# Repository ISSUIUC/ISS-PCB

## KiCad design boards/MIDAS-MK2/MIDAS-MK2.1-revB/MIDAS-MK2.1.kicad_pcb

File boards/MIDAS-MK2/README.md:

# MIDAS MK2

MIDAS MK2 is the new and improved generation of the Illinois Space Society's MIDAS flight computer. Continuing MIDAS’s mission as the centerpiece of a flexible avionics ecosystem, MK2 features data acquisition, live telemetry, board-to-board communication interfaces, and pyrotechnic capabilities for in-flight control. This new revision retains the diverse suite of sensors from the original and features upgraded pyro circuitry with an emphasis on redundancy and reliability. As the team pushes closer and closer to space, MK2 employs a new generation of LoRa radios with 60% higher transmit power as well as CAN and I2C connections for future expandability into satellite communications and other more advanced tracking capabilities. This adaptable nature has enabled MIDAS to fulfill various roles, not only as a flight computer but also as a part of the team’s onboard video system and as a major ground support device. Overall, these across-the-board improvements have pushed the MIDAS project to new heights and led to a string of successes in each of its many domains.

Three MIDAS MK2 boards have been produced, with the series successfully flying in flight control of the Stargazer 1.4 vehicle and as the primary tracker for Aether I & II, the latter of which flew to an altitude of 75,000 feet.

Read more about MIDAS and the surrounding avionics systems in the [MIDAS MK2 Report](https://uofi.box.com/s/k0ad6ryhxbzwpdwt33lxyxuxpivv3qhj).

# Schematics

Printable PDF schematics, diagrams, and layouts for MIDAS MK2.1 revA can be found in the PDFs and images folders.

# Graphics

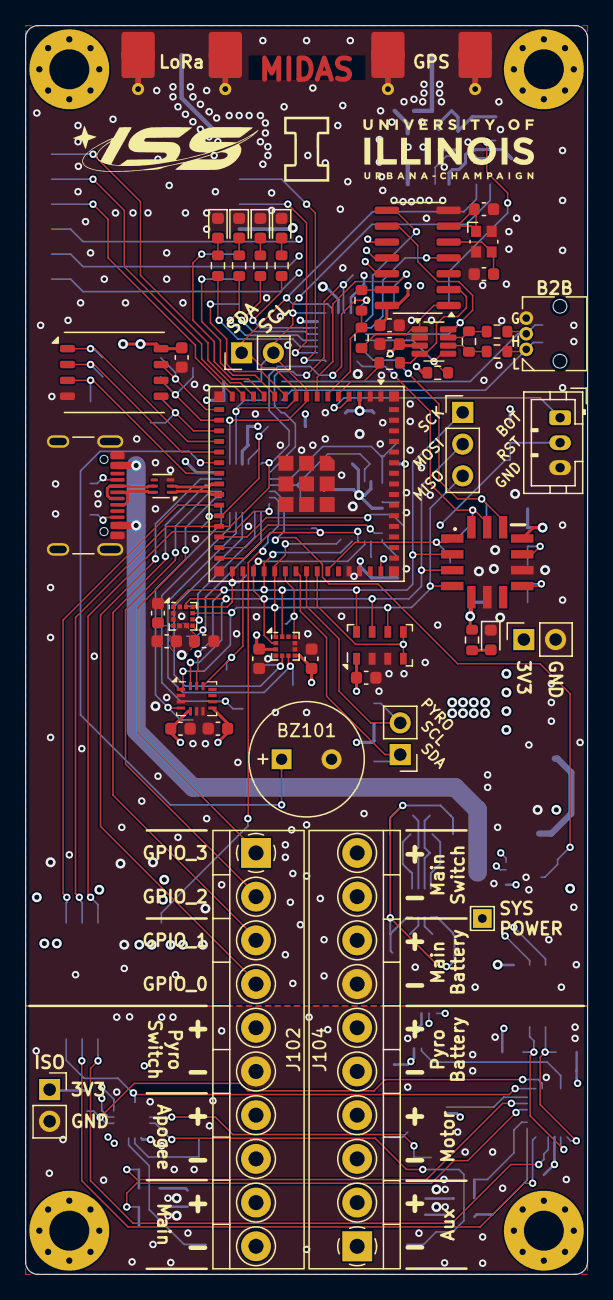
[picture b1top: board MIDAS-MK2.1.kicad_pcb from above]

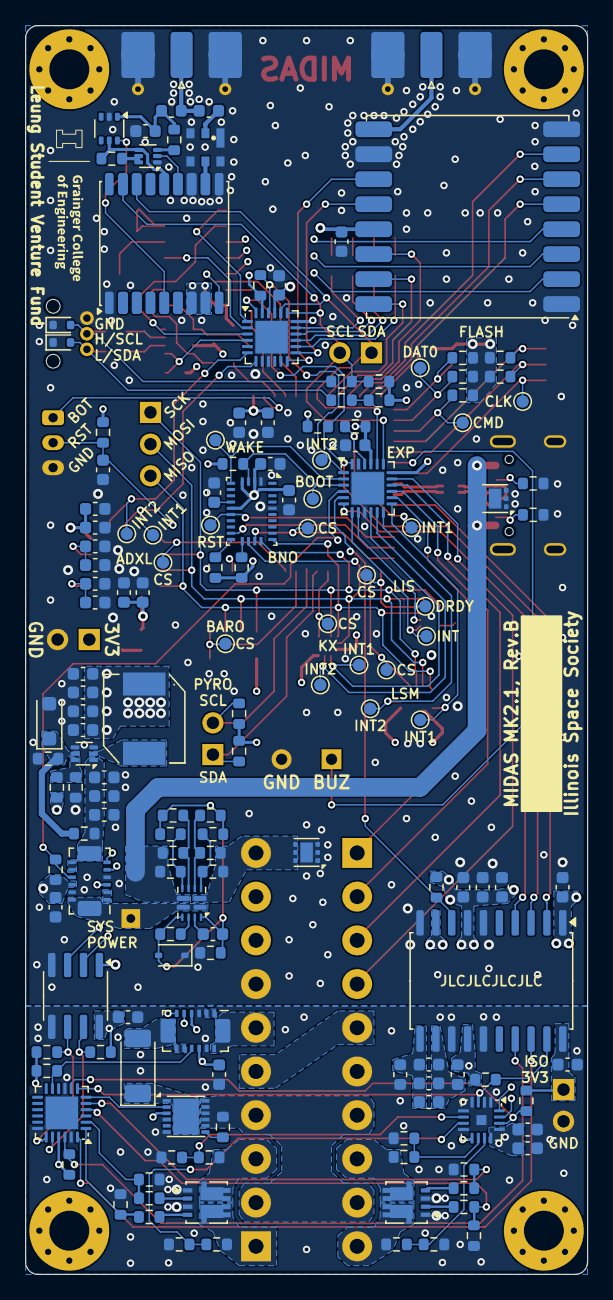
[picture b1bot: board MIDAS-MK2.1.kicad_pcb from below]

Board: 4 copper layers, 45.0 x 100.0 mm, 212 parts (155 on the bottom side), 155 nets.

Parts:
BZ101: AT-0927-TT-6-R; Buzzer_AT-0927-TT-6-R
C101, C102, C103, C107, C108, C109, C110, C201, C208, C209, C210, C211, C212, C301, C502, C504, C506, C507, C508, C510, C511, C512, C513, C514, C515, C517, C518, C519: 0.1uF; C_0603_1608Metric
C104, C105: 22pF; C_0603_1608Metric
C106, C304, C305, C306, C307: 22uF; C_0603_1608Metric
C111, C204, C205, C308, C501, C503, C505, C509, C516: 1uF; C_0603_1608Metric
C202, C203, C402: 10nF; C_0603_1608Metric
C206, C207, C302, C303, C401: 10uF; C_0603_1608Metric
C403: 47pF; C_0603_1608Metric
D101, D102: ESD321; D_SOD-523
D103, D303: RED LED; LED_0603_1608Metric
D104: ORANGE LED; LED_0603_1608Metric
D105: GREEN LED; LED_0603_1608Metric
D106: BLUE LED; LED_0603_1608Metric
D201: RSX501LAM20; D_SOD-128
D301: BZT52H-A5V1-QX; D_SOD-123F
D302: BAS416; D_SOD-323
FB201, FB202: BLM18SG331TN1D; L_0603_1608Metric
FL401: B3913; Qualcomm_SMD-6
H101, H102, H103, H104: M3; MountingHole_3.2mm_M3_Pad_Via
J101: USB4105-GF-A; USB_C_Receptacle_GCT_USB4105-xx-A_16P_TopMnt_Horizontal
J102: Left; Molex_Terminal-Block_393570010_1x10_P3.5mm
J103: Conn_01x03; Molex_Micro-Lock_2200980371_1x03_P1.25mm_Horizontal
J104: Right; Molex_Terminal-Block_393570010_1x10_P3.5mm
J105, J106: Conn_01x02; PinHeader_1x02_P2.54mm_Vertical
J107: Conn_01x03; PinHeader_1x03_P2.54mm_Vertical
J108: Conn_01x03; JST_PH_B3B-PH-K_1x03_P2.00mm_Vertical
J201, J302: Conn_01x02; PinSocket_1x02_P2.54mm_Vertical
J301: TestPoint; TestPoint_THTPad_1.5x1.5mm_Drill0.7mm
J401, J402: SMA; SMA_Molex_73251-2120_EdgeMount_Horizontal
L301: 2.2uH; L_TDK_SPM6530
L401: 27nH; L_0603_1608Metric
Q201, Q202: Si7232DN; Vishay_PowerPAK_1212-8_Dual
Q401: Si1016X; SOT-563
R101, R104, R105, R106, R220, R222: 4.7k; R_0603_1608Metric
R102, R103, R107, R108, R114, R201, R221, R223, R224, R501: 10k; R_0603_1608Metric
R109, R110, R111, R112, R113: 50k; R_0603_1608Metric
R115, R116, R117, R118, R119, R120, R121, R312: 0; R_0603_1608Metric
R122: 120; R_0603_1608Metric
R123, R124: 5.1k; R_0603_1608Metric
R125, R303: 20k; R_0603_1608Metric
R126, R127, R128, R129, R315: 470; R_0603_1608Metric
R202, R206, R207, R214, R215: 1k; R_0603_1608Metric
R203, R301, R302, R305, R308, R310: 5k; R_0603_1608Metric
R204, R205, R212, R213: 3.3k; R_0603_1608Metric
R208, R209, R216, R217, R402: 100k; R_0603_1608Metric
R210, R211, R218, R219, R306, R311: 30k; R_0603_1608Metric
R304: 27k; R_0603_1608Metric
R307: 33k; R_0603_1608Metric
R309: 69.8k; R_0603_1608Metric
R313: 135k; R_0603_1608Metric
R314: 21.5k; R_0603_1608Metric
R401: 10; R_0603_1608Metric
R502, R503: 2.2k; R_0603_1608Metric
TP101, TP102, TP103, TP104, TP105, TP106, TP107, TP108, TP109, TP110, TP111, TP112, TP113, TP114, TP115, TP116, TP117, TP118, TP119, TP120, TP121, TP122: TestPoint_Small; TestPoint_Pad_D1.0mm
U101, U201: INA745x; VQFN-REL0014B
U102, U103, U205: TCAL9539-Q1; WQFN-24-1EP_4x4mm_P0.5mm_EP2.6x2.6mm
U104: ESP32-S3-MINI-1U; ESP32-S2-MINI-1U
U105: MCP2518FDT-xSL; SOIC-14_3.9x8.7mm_P1.27mm
U106: ZDSD64GLGEAG-R; LGA-8_8x6.2mm_P1.27mm
U107: TCAN337G; SOT-23-8
U108: ECMF02-2AMX6; ST_UQFN-6L_1.5x1.7mm_P0.5mm
U202: NPC45560-H; DFN-12-1EP_3x3mm_P0.5mm_EP2.05x2.86mm
U203: ISOW7742; SOIC-20W_7.5x12.8mm_P1.27mm
U204: ISO1640BDR; SOIC-8_3.9x4.9mm_P1.27mm
U206: ADS122C04IRTE; Texas_RTE0016D_WQFN-16-1EP_3x3mm_P0.5mm_EP0.8x0.8mm
U301, U302: TVS1800DRV; WSON-6-1EP_2x2mm_P0.65mm_EP1x1.6mm
U303: TI_TPS566242; SOT-563
U304: TPS2121; Texas_VQFN-HR-12_2x2.5mm_P0.5mm
U401: RFM96W-433S2; HOPERF_RFM9XW_SMD
U402: NC7WZ07; SOT-363_SC-70-6
U403: MAX-M10S; ublox_MAX
U501: KX134-1211; LGA-12_2x2mm_P0.5mm
U502: ADXL355; Analog_LGA_14-7.4x7.4mm
U503: LSM6DSLTR; Bosch_LGA-14_3x2.5mm_P0.5mm
U504: BNO086; LGA-28_5.2x3.8mm_P0.5mm
U505: LIS3MDL; LGA-12_2x2mm_P0.5mm
U506: MS5611-01BA03; LGA-8_3x5mm_P1.25mm
Y101: 40MHz; Crystal_SMD_Abracon_ABM10-4Pin_2.5x2.0mm

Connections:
+3V3: C101.2, C102.1, C103.1, C106.2, C107.2, C108.2, C109.2, C110.2, C202.1, C204.1, C206.1, C209.1, C304.1, C305.1, C306.1, C307.1, C401.1, C501.2, C502.2, C503.2, C504.1, C506.1, C508.1, C511.1, C512.1, C514.1, C515.1, C516.2, C517.2, C519.1, J302.1, L301.1, R101.2, R102.2, R103.2, R104.2, R105.2, R106.2, R107.1, R108.2, R109.2, R110.2, R111.2, R112.2, R113.2, R114.1, R125.2, R203.1, R313.2, R315.1, R501.2, R502.2, R503.2, U101.3 (A1), U101.11 (VS), U102.18 (A0), U102.21 (VCC), U103.18 (A0), U103.21 (VCC), U103.23 (A1), U104.3 (3V3), U105.14 (VDD), U106.8 (VDD), U107.3 (VCC), U203.1 (V_{IO}), U203.7 (EN_IO1), U203.9 (V_{DD}), U204.1 (VCC1), U401.13 (3.3V), U403.7 (VCC_IO), U403.8 (VCC), U501.3 (IO_VDD), U501.7 (VDD), U502.5 (V_{DDIO}), U502.11 (V_{SUPPLY}), U503.5 (VDDIO), U503.8 (VDD), U504.3 (VDD), U504.5 (PS1), U504.10 (CLKSEL0), U504.28 (VDDIO), U505.5 (Vdd), U505.6 (Vdd_IO), U506.1 (VDD)
+3V3_ISO: C201.2, C208.1, C210.1, C211.1, C212.1, FB201.1, J201.1, R201.1, R220.2, R221.2, R222.2, R223.2, R224.2, U201.4 (A0), U201.11 (VS), U202.3 (VCC), U203.14 (EN_IO2), U203.20 (V_{ISOIN}), U204.8 (VCC2), U205.21 (VCC), U206.9 (REFP), U206.12 (AVDD), U206.13 (DVDD)
/ADC_RESET: U104.25 (IO21), U203.2 (INA)
/ADXL355_CS: TP107.1, U104.40 (RXD0), U502.1 (~CS/SCL)
/ADXL355_INT1: TP109.1, U103.7 (P06), U502.13 (INT2)
/ADXL355_INT2: TP108.1, U103.6 (P05), U502.12 (INT1)
/AUX_GPIO_0: J102.4, U102.17
/AUX_GPIO_1: J102.3, U102.16
/AUX_GPIO_2: J102.2, U102.15
/AUX_GPIO_3: J102.1, U102.14
/BNO086_BOOT: R501.1, TP106.1, U102.3 (P02), U504.4 (BOOTN)
/BNO086_CS: TP103.1, U104.30 (IO48), U504.18 (H_CSN)
/BNO086_INT: U104.29 (IO34), U504.14 (H_INTN)
/BNO086_RESET: TP104.1, U104.28 (IO33), U504.11 (NRST)
/BNO086_WAKE: TP105.1, U102.2 (P01), U504.6 (PS0/WAKE)
/BOOT_SW: J108.1, U104.4 (IO0)
/BUZZER: BZ101.1 (-), U104.21 (IO17)
/CANH: R117.1, R122.1, U107.7 (CANH)
/CANL: R115.1, R122.2, U107.6 (CANL)
/CAN_1: R119.1, R120.1, U104.6 (IO2)
/CAN_2: R121.1, U104.5 (IO1)
/CAN_FAULT: R114.2, U103.4 (P03), U107.5 (FAULT)
/CAN_NCS: R119.2, U105.13 (NCS)
/CAN_NINT: U103.2 (P01), U105.4 (~INT)
/CAN_NINT1: U103.1 (P00), U105.8 (~INT1/GPIO1)
/CAN_RXD: R121.2, U105.2 (RXCAN), U107.4 (RXD)
/CAN_SLNT: U103.3 (P02), U105.9 (~INT0/GPIO0/XSTBY), U107.8 (S)
/CAN_TXD: R120.2, U105.1 (TXCAN), U107.1 (TXD)
/D+: J101.A6 (D+), J101.B6 (D+), U108.6 (D+_out)
/D-: J101.A7 (D-), J101.B7 (D-), U108.5 (D-_out)
/EXP_INT0: U102.6 (P05), U203.4 (OUTC)
/EXP_INT1: R102.1, TP101.1, U102.22 (~INT), U104.26 (IO26)
/EXP_INT2: R103.1, TP102.1, U102.1 (P00), U103.22 (~INT)
/EXP_RESET: R108.1, U102.24 (~RESET), U103.24 (~RESET), U104.27 (IO47), U203.3 (INB)
/FLASH_CLK: TP121.1, U104.22 (IO18), U106.3 (CLK)
/FLASH_CMD: R113.1, TP120.1, U104.18 (IO14), U106.5 (CMD)
/FLASH_DAT0: R109.1, TP122.1, U104.17 (IO13), U106.6 (DAT0)
/FLASH_DAT1: R110.1, U104.16 (IO12), U106.7 (DAT1)
/FLASH_DAT2: R111.1, U104.19 (IO15), U106.1 (DAT2)
/FLASH_DAT3: R112.1, U104.20 (IO16), U106.2 (DAT3)
/I2C_SCL: J105.2, R104.1, R118.1, U102.19 (SCL), U103.19 (SCL), U104.8 (IO4), U403.17 (SCL)
/I2C_SDA: J105.1, R101.1, R116.1, U102.20 (SDA), U103.20 (SDA), U104.9 (IO5), U403.16 (SDA)
/INA_ALERT: R107.2, U101.10 (ALERT), U102.4 (P03)
/ISO_FLT: R203.2, U102.5 (P04), U203.8 (EN/FLT)
/KX134_CS: TP110.1, U104.36 (IO40), U501.10 (nCS)
/KX134_INT1: TP112.1, U102.10, U501.5 (INT1)
/KX134_INT2: TP111.1, U102.11, U501.6 (INT2)
/LED_BLUE: R129.1, U103.14
/LED_GREEN: R128.1, U103.15
/LED_ORANGE: R127.1, U103.16
/LED_RED: R126.1, U103.17
/LIS3MDL_CS: TP113.1, U104.31 (IO35), U505.10 (CS)
/LIS3MDL_DRDY: TP114.1, U102.8 (P07), U505.8 (DRDY)
/LIS3MDL_INT: TP115.1, U102.7 (P06), U505.7 (INT)
/LSM6DSLTR_INT1: TP117.1, U102.13, U503.4 (INT1)
/LSM6DSLTR_INT2: TP118.1, U102.12, U503.9 (INT2)
/LSM6DSL_CS: TP116.1, U104.32 (IO36), U503.12 (CS)
/MAX_RESET: U104.7 (IO3), U403.9 (~RESET)
/MS5611_CS: TP119.1, U104.39 (TXD0), U506.4 (CSB), U506.5 (CSB)
/PYRO_A: J102.8, Q201.5 (D2), R208.2
/PYRO_B: J102.10, Q201.6 (D1), R216.2
/PYRO_C: J104.3, Q202.6 (D1), R209.2
/PYRO_D: J104.1, Q202.5 (D2), R217.2
/PYRO_SCL: J106.2, R106.1, U101.6 (SCL), U104.38 (IO42), U204.3 (SCL1)
/PYRO_SDA: J106.1, R105.1, U101.5 (SDA), U104.37 (IO41), U204.2 (SDA1)
/PYRO_SW: J102.5, J104.5
/Power/MUX_CP2: R307.2, R308.1, U304.3 (CP2)
/Pyro Circuitry/ADC_DRDY: R224.1, U205.8 (P07), U206.14 (DRDY)
/Pyro Circuitry/ADC_RST_ISO: R223.1, U203.19 (OUTA), U205.7 (P06), U206.3 (RESET)
/Pyro Circuitry/EXP_INT_ISO: R221.1, U203.17 (INC), U205.22 (~INT)
/Pyro Circuitry/EXP_RST_ISO: U203.18 (OUTB), U205.24 (~RESET)
/Pyro Circuitry/FIRE_A: R204.1, R206.1, U205.5 (P04)
/Pyro Circuitry/FIRE_B: R212.1, R214.1, U205.4 (P03)
/Pyro Circuitry/FIRE_C: R205.1, R207.1, U205.2 (P01)
/Pyro Circuitry/FIRE_D: R213.1, R215.1, U205.1 (P00)
/Pyro Circuitry/GND2: C203.2, C205.2, C207.2, FB202.2, U203.11 (GND2)
/Pyro Circuitry/INA_ALRT_ISO: R201.2, U201.10 (ALERT), U205.11
/Pyro Circuitry/ISO_SCL: R222.1, U201.6 (SCL), U204.6 (SCL2), U205.19 (SCL), U206.16 (SCL)
/Pyro Circuitry/ISO_SDA: R220.1, U201.5 (SDA), U204.7 (SDA2), U205.20 (SDA), U206.15 (SDA)
/Pyro Circuitry/PYRO_EN: U202.2 (EN), U205.6 (P05)
/Pyro Circuitry/SENSE_A: R208.1, R210.2, U206.10 (AIN1)
/Pyro Circuitry/SENSE_B: R216.1, R218.2, U206.11 (AIN0)
/Pyro Circuitry/SENSE_C: R209.1, R211.2, U206.6 (AIN3)
/Pyro Circuitry/SENSE_D: R217.1, R219.2, U206.7 (AIN2)
/Pyro Circuitry/V_ISOOUT: C203.1, C205.1, C207.1, FB201.2, U203.12 (V_{ISOOUT})
/Pyro Circuitry/V_PYRO_ZONE: D201.2 (A), U201.7 (IS-)
/RESET_SW: C111.1, J108.2, R125.1, U104.45 (EN)
/RF/MAX_INT: U402.6 (Y1), U403.5 (EXTINT)
/RFM96W_CS: U104.15 (IO11), U401.5 (NSS)
/RFM96W_DIO1: U104.11 (IO7), U401.15 (DIO1)
/RFM96W_DIO2: U104.10 (IO6), U401.16 (DIO2)
/RFM96W_DIO3: U103.12, U401.11 (DIO3)
/RFM96W_DIO4: U103.13, U401.12 (DIO4)
/RFM96W_DIO5: U104.13 (IO9), U401.7 (DIO5)
/RFM96W_INT: U104.12 (IO8), U401.14 (DIO0)
/RFM96W_RESET: U104.14 (IO10), U401.6 (RESET)
/SPI_MISO: J107.3, U104.35 (IO39), U105.12 (SDO), U401.2 (MISO), U501.1 (SDO/ADDR), U502.4 (MISO/ASEL), U503.1 (SDO/SA0), U504.20 (H_SDA/H_MISO/TX), U505.9 (SDO/SA1), U506.6 (SDO)
/SPI_MOSI: J107.2, U104.33 (IO37), U105.11 (SDI), U401.3 (MOSI), U501.2 (SDI/SDA), U502.3 (MOSI/SDA), U503.14 (SDA), U504.17 (H_SA0_MOSI), U505.11 (SDA/SDI/SDO), U506.7 (SDI/SDA)
/SPI_SCK: J107.1, U104.34 (IO38), U105.10 (SCK), U401.4 (SCK), U501.12 (SCLK/SCL), U502.2 (SCLK/V_{SSIO}), U503.13 (SCL), U504.19 (H_SCL/SCK/RX), U505.1 (SCL/SPC), U506.8 (SCLK)
/SYS_POWER: J301.1, U101.13 (VBUS), U101.14 (IS+), U304.1 (OUT), U304.8 (OUT)
/USB_D+: U104.24 (IO20), U108.1 (D+_in)
/USB_D-: U104.23 (IO19), U108.2 (D-_in)
/USB_POWER: J101.A4 (VBUS), J101.A9 (VBUS), J101.B4 (VBUS), J101.B9 (VBUS), R301.1, R304.1, U301.4 (IN), U301.5 (IN), U301.6 (IN), U304.7 (IN1)
/VBAT: J104.10, R307.1, R309.1, U302.4 (IN), U302.5 (IN), U302.6 (IN), U304.2 (IN2)
/VBAT_PYRO: J104.6, U201.13 (VBUS), U201.14 (IS+)
/VREG_IN: C301.1, C302.1, C303.1, R303.1, U101.7 (IS-), U303.1 (VIN)
/V_PYRO: J102.7, J102.9, J104.2, J104.4, R202.1, U202.8 (VOUT), U202.9 (VOUT), U202.10 (VOUT), U202.11 (VOUT), U202.12 (VOUT)
GND: BZ101.2 (+), C101.1, C102.2, C103.2, C104.1, C105.2, C106.1, C107.1, C108.1, C109.1, C110.1, C111.2, C202.2, C204.2, C206.2, C209.2, C301.2, C302.2, C303.2, C304.2, C305.2, C306.2, C307.2, C401.2, C402.2, C501.1, C502.1, C503.1, C504.2, C505.1, C506.2, C507.2, C508.2, C509.1, C510.2, C511.2, C512.2, C513.2, C514.2, C515.2, C516.1, C517.1, C518.1, C519.2, D101.1 (A1), D102.1 (A1), D103.1 (K), D104.1 (K), D105.1 (K), D106.1 (K), D301.2 (A), D302.1 (K), D303.1 (K), FL401.1 (GND), FL401.3 (GND), FL401.4 (GND), FL401.6 (GND), J101.A1 (GND), J101.A12 (GND), J101.B1 (GND), J101.B12 (GND), J101.S1 (SHIELD), J103.3, J104.7, J108.3, J302.2, J401.2 (Ext), J402.2 (Ext), Q401.1 (S1), R123.2, R124.2, R306.2, R311.2, R312.2, U101.4 (A0), U101.12 (GND), U102.9 (GND), U102.23 (A1), U102.25 (GND), U103.9 (GND), U103.25 (GND), U104.1 (GND), U104.2 (GND), U104.42 (GND), U104.43 (GND), U104.46 (GND), U104.47 (GND), U104.48 (GND), U104.49 (GND), U104.50 (GND), U104.51 (GND), U104.52 (GND), U104.53 (GND), U104.54 (GND), U104.55 (GND), U104.56 (GND), U104.57 (GND), U104.58 (GND), U104.59 (GND), U104.60 (GND), U104.61 (GND), U104.62 (GND), U104.63 (GND), U104.64 (GND), U104.65 (GND), U105.7 (VSS), U106.4 (GND), U107.2 (GND), U108.3 (GND), U203.6 (GNDIO), U203.10 (GND1), U204.4 (GND1), U301.1 (GND), U301.2 (GND), U301.3 (GND), U301.7 (GND), U302.1 (GND), U302.2 (GND), U302.3 (GND), U302.7 (GND), U303.3 (GND), U303.4 (AGND), U401.1 (GND), U401.8 (GND), U401.10 (GND), U402.2 (GND), U403.1 (GND), U403.10 (GND), U403.12 (GND), U501.4 (TRIG), U501.8 (GND), U501.9 (GND), U502.6 (V_{SSIO}), U502.9 (VSS), U503.2 (SDx), U503.3 (SCx), U503.6 (GND), U503.7 (GND), U504.2 (GND), U504.25 (GNDIO), U505.2 (Reserved), U505.3 (GND), U505.12 (Reserved), U506.2 (PS), U506.3 (GND), Y101.2, Y101.4
unnamed: D101.2 (A2), J103.1, R115.2, R116.2
unnamed: D102.2 (A2), J103.2, R117.2, R118.2
unnamed: D103.2 (A), R126.2
unnamed: D104.2 (A), R127.2
unnamed: D105.2 (A), R128.2
unnamed: D106.2 (A), R129.2
unnamed: D201.1 (K), U202.1 (VIN), U202.13 (VIN)
unnamed: D301.1 (K), R303.2, R306.1, U303.5 (EN)
unnamed: C308.1, D302.2 (A), R302.2, R305.2, R308.2, R310.2, R312.1, R314.1, U304.9 (ST), U304.12 (GND)
unnamed: D303.2 (A), R315.2
unnamed: C403.2, FL401.2 (IN)
unnamed: FL401.5 (OUT), U403.11 (RF_IN)
unnamed: J101.A5 (CC1), R123.1
unnamed: J101.B5 (CC2), R124.1
unnamed: J104.8, J104.9
unnamed: C403.1, J401.1 (In), L401.1
unnamed: J402.1 (In), U401.9 (ANT)
unnamed: Q201.2 (G1), R214.2
unnamed: Q201.4 (G2), R206.2
unnamed: Q202.2 (G1), R207.2
unnamed: Q202.4 (G2), R215.2
unnamed: Q401.5 (G2), Q401.6 (D1), R402.1
unnamed: Q401.2 (G2), U403.13 (LNA_EN)
unnamed: Q401.3 (D2), R401.1
unnamed: Q401.4 (S2), R402.2, U402.5 (VCC), U403.14 (VCC_RF)
unnamed: U101.1 (SH+), U101.2 (IN+)
unnamed: U101.8 (SH-), U101.9 (IN-)
unnamed: C105.1, U105.6 (OSC1), Y101.1
unnamed: C104.2, U105.5 (OSC2), Y101.3
unnamed: U201.1 (SH+), U201.2 (IN+)
unnamed: U201.8 (SH-), U201.9 (IN-)
unnamed: R202.2, U202.7 (BLEED)
unnamed: R311.1, R313.1, U303.6 (FB)
unnamed: L301.2, U303.2 (SW)
unnamed: R314.2, U304.10 (ILM)
unnamed: R304.2, R305.1, U304.5 (OV1)
unnamed: R309.2, R310.1, U304.4 (OV2)
unnamed: R301.2, R302.1, U304.6 (PR1)
unnamed: C308.2, U304.11 (SS)
unnamed: C402.1, L401.2, R401.2, U402.1 (A1)
unnamed: C505.2, C507.1, U502.10 (V_{1P8ANA})
unnamed: C509.2, C510.1, U502.8 (V_{1P8DIG})
unnamed: C513.1, U504.9 (CAP)
unnamed: R503.1, U504.15 (ENV_SCL)
unnamed: R502.1, U504.16 (ENV_SDA)
unnamed: C518.2, U505.4 (C1)
PYRO_GND: C201.1, C208.2, C210.2, C211.2, C212.2, FB202.1, J102.6, J201.2, Q201.1 (S1), Q201.3 (S2), Q202.1 (S1), Q202.3 (S2), R204.2, R205.2, R210.1, R211.1, R212.2, R213.2, R218.1, R219.1, U201.3 (A1), U201.12 (GND), U202.4 (GND), U202.6 (PG), U203.13 (VSEL), U203.15 (GISOIN), U204.5 (GND2), U205.9 (GND), U205.18 (A0), U205.23 (A1), U205.25 (GND), U206.1 (A0), U206.2 (A1), U206.4 (DGND), U206.5 (AVSS), U206.8 (REFN), U206.17 (EP)

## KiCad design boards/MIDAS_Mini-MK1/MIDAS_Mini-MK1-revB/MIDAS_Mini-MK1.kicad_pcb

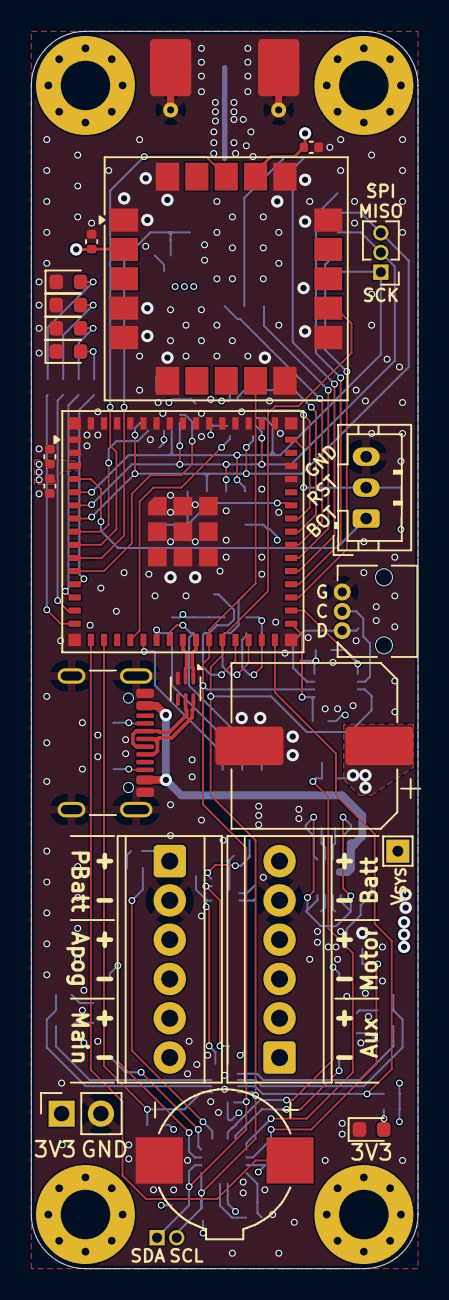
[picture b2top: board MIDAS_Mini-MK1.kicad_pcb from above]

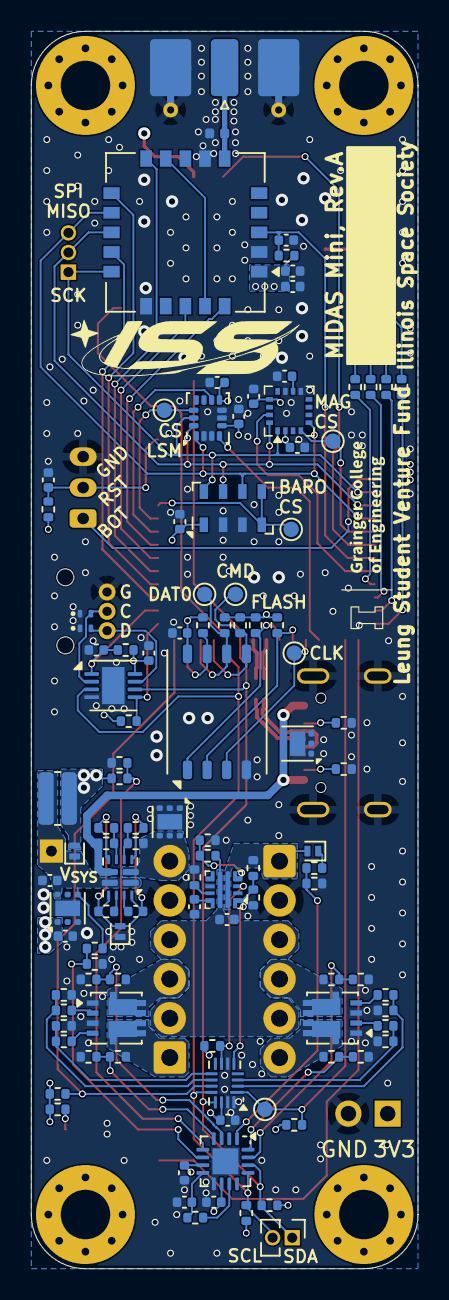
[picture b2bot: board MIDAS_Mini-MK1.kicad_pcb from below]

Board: 4 copper layers, 25.0 x 80.0 mm, 133 parts (107 on the bottom side), 91 nets.

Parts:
BZ101: Buzzer; Buzzer_SMTB-0927-TW-R
C101, C102, C103, C112, C201, C202: 1uF; C_0402_1005Metric
C104: 22uF; C_0402_1005Metric
C105, C106, C107, C108, C109, C113, C114, C301, C302, C304, C305, C306, C403: 100nF; C_0402_1005Metric
C110, C303: 10uF; C_0402_1005Metric
C111: 10nF; C_0402_1005Metric
C203: 220mF; CP_Elec_10x10.5
C204, C402: 4.7uF; C_0402_1005Metric
C401: 4.7nF; C_0402_1005Metric
D101, D202: SDM05U40CSP; D_SOD-882
D102, D103: ESD321; Texas_DPY0002A_0.6x1mm_P0.65mm
D104, D203: RED LED; LED_0603_1608Metric
D105: ORANGE LED; LED_0603_1608Metric
D106: GREEN LED; LED_0603_1608Metric
D107: BLUE LED; LED_0603_1608Metric
D201: BAS116L; D_SOD-882
H101, H102, H103, H104: M3; MountingHole_3.2mm_M3_Pad_Via
J101: USB4105-GF-A; USB_C_Receptacle_GCT_USB4105-xx-A_16P_TopMnt_Horizontal
J102, J103: Screw_Terminal_01x06; TerminalBlock_TE_282834-6_1x06_P2.54mm_Horizontal
J104: Conn_01x03; Molex_Micro-Lock_2200980371_1x03_P1.25mm_Horizontal
J105: SMA; SMA_Molex_73251-2120_EdgeMount_Horizontal
J106: Conn_01x03; PinHeader_1x03_P1.27mm_Vertical
J107: Conn_01x02; PinHeader_1x02_P1.27mm_Vertical
J108: Conn_01x03; JST_PH_B3B-PH-K_1x03_P2.00mm_Vertical
J201: TestPoint; TestPoint_THTPad_1.5x1.5mm_Drill0.7mm
J202: Conn_01x02; PinSocket_1x02_P2.54mm_Vertical
L101: 330nH; L_0402_1005Metric
Q401, Q402: Si7232DN; Vishay_PowerPAK_1212-8_Dual
R101, R103, R104, R105, R108, R109, R116, R404, R407, R408, R414, R419, R420: 100k; R_0402_1005Metric
R102: 560k; R_0402_1005Metric
R106, R107: 5.1k; R_0402_1005Metric
R110, R111, R112, R113, R114: 50k; R_0402_1005Metric
R115, R119, R423, R424: 10k; R_0402_1005Metric
R117, R118: 4.7k; R_0402_1005Metric
R120: 20k; R_0402_1005Metric
R121, R122, R123, R124, R207: 470; R_0402_1005Metric
R201, R203: 16.9k; R_0402_1005Metric
R202, R204: 5k; R_0402_1005Metric
R205: 21.5k; R_0402_1005Metric
R206: 20; R_0612_1632Metric
R401, R402, R415, R416: 3.3k; R_0402_1005Metric
R403, R413: 150k; R_0402_1005Metric
R405, R406, R412, R417, R418: 1k; R_0402_1005Metric
R409, R410, R421, R422: 18k; R_0402_1005Metric
R411: 820; R_0402_1005Metric
TP101, TP102, TP103, TP104, TP105, TP106, TP107: TestPoint_Small; TestPoint_Pad_D1.0mm
U101: ADS7138-Q1; WQFN-16-1EP_3x3mm_P0.5mm_EP1.68x1.68mm
U102: ECMF02-2AMX6; ST_UQFN-6L_1.5x1.7mm_P0.5mm
U103: ESP32-S3-MINI-1U; ESP32-S2-MINI-1U
U104: ZDSD64GLGEAG-R; LGA-8_8x6.2mm_P1.27mm
U105: TCA4307; WSON-8-1EP_3x3mm_P0.5mm_EP1.45x2.4mm
U106: E22-400MM22S
U107: SAM-M10Q; ublox_SAM-M8Q
U201, U202: TVS1800DRV; WSON-6-1EP_2x2mm_P0.65mm_EP1x1.6mm
U203: TPS2121; Texas_VQFN-HR-12_2x2.5mm_P0.5mm
U204: TPS746-Q1; WSON-6-1EP_2x2mm_P0.65mm_EP1x1.6mm
U301: MMC5983MA; LGA-16_3x3mm_P0.5mm
U302: LSM6DSV320X; LGA-14_3x2.5mm_P0.5mm_LayoutBorder3x4y
U303: MS5611-01BA; LGA-8_3x5mm_P1.25mm
U401: TPS25947; VQFN-HR-RPW0010A
U402: TCAL9538; UQFN-16_1.8x2.6mm_P0.4mm

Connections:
+3V3: C102.1, C103.1, C104.1, C105.1, C106.2, C109.1, C110.1, C111.1, C113.2, C114.2, C204.1, C301.1, C302.1, C304.1, C305.1, C306.1, C403.2, J202.1, R110.2, R111.2, R112.2, R113.2, R114.2, R115.2, R116.2, R117.2, R118.2, R119.2, R120.2, R207.1, R412.2, R423.2, R424.2, U101.7 (AVDD), U101.10 (DVDD), U103.3 (3V3), U104.8 (VDD), U105.8 (VCC), U106.1 (VCC), U107.2 (VCC_IO), U107.17 (VCC), U204.1 (OUT), U301.2 (VDD), U301.13 (VDDIO), U302.5 (VDDIO), U302.8 (VDD), U303.1 (VDD), U402.14 (VCC)
/B2B_EN: C107.1, R115.1, U103.32 (IO36), U105.1 (EN)
/B2B_READY: R119.1, U103.31 (IO35), U105.5 (READY)
/BOOT_SW: J108.1, U103.4 (IO0)
/BUZZER: BZ101.1 (+), U103.16 (IO12)
/D+: J101.A6 (D+), J101.B6 (D+), U102.6 (D+_out)
/D-: J101.A7 (D-), J101.B7 (D-), U102.5 (D-_out)
/E22_BUSY: U103.34 (IO38), U106.11 (BUSY)
/E22_CS: U103.33 (IO37), U106.14 (NSS)
/E22_DIO1: U103.37 (IO41), U106.20 (DIO1)
/E22_DIO3: U103.36 (IO40), U106.18 (DIO3)
/E22_RESET: C108.1, R116.1, U103.10 (IO6), U106.3 (NRST)
/E22_RXEN: U103.35 (IO39), U106.10 (RXEN)
/EXP_INT: R424.1, U103.30 (IO48), U402.11 (INT)
/EXP_RESET: R423.1, TP101.1, U103.17 (IO13), U402.1 (~RESET)
/FLASH_CLK: TP106.1, U103.20 (IO16), U104.3 (CLK)
/FLASH_CMD: R114.1, TP105.1, U103.27 (IO47), U104.5 (CMD)
/FLASH_DAT0: R110.1, TP107.1, U103.28 (IO33), U104.6 (DAT0)
/FLASH_DAT1: R111.1, U103.29 (IO34), U104.7 (DAT1)
/FLASH_DAT2: R112.1, U103.22 (IO18), U104.1 (DAT2)
/FLASH_DAT3: R113.1, U103.21 (IO17), U104.2 (DAT3)
/I2C_SCL: J107.2, R118.1, U101.13 (SCL), U103.26 (IO26), U105.3 (SCLIN), U107.12 (SCL), U402.12 (SCL)
/I2C_SCL_B2B: D103.2 (A2), J104.2, U105.2 (SCLOUT)
/I2C_SDA: J107.1, R117.1, U101.14 (SDA), U103.25 (IO21), U105.6 (SDAIN), U107.9 (SDA), U402.13 (SDA)
/I2C_SDA_B2B: D102.2 (A2), J104.1, U105.7 (SDAOUT)
/LED_BLUE: R124.1, U103.12 (IO8)
/LED_GREEN: R123.1, U103.13 (IO9)
/LED_ORANGE: R122.1, U103.14 (IO10)
/LED_RED: R121.1, U103.15 (IO11)
/LSM_CS: TP104.1, U103.39 (TXD0), U302.12 (CS)
/LSM_INT1: U103.19 (IO15), U302.4 (INT1)
/LSM_INT2: U103.38 (IO42), U302.9 (INT2)
/MAG_CS: TP102.1, U103.8 (IO4), U301.4 (CS)
/MAG_INT: U103.11 (IO7), U301.15 (INT)
/MS5611_CS: TP103.1, U103.40 (RXD0), U303.4 (CSB), U303.5 (CSB)
/PYRO_A: J102.4, Q401.5 (D2), R407.2
/PYRO_B: J102.6, Q401.6 (D1), R419.2
/PYRO_C: J103.3, Q402.6 (D1), R408.2
/PYRO_D: J103.1, Q402.5 (D2), R420.2
/PYRO_SENSE: R102.2, R103.1, U101.1 (ANI2/GPIO2)
/Power/PMUX_GND: C201.1, D201.2 (A), R202.2, R204.2, R205.1, U203.3 (CP2), U203.6 (PR1), U203.9 (ST), U203.12 (GND)
/Pyro/FIRE_A: R401.1, R405.1, U402.2 (P0)
/Pyro/FIRE_B: R415.1, R417.1, U402.3 (P1)
/Pyro/FIRE_C: R402.1, R406.1, U402.10 (P7)
/Pyro/FIRE_D: R416.1, R418.1, U402.9 (P6)
/Pyro/PGTH: R413.2, R414.1, U401.4 (PGTH/NFLT)
/Pyro/PYRO_EN: R403.2, R404.1, U401.1 (EN/UVLO), U402.5 (P3)
/Pyro/PYRO_PG: R412.1, U401.3 (PG/AUXOFF), U402.7 (P4)
/RESET_SW: C112.1, J108.2, R120.1, U103.45 (EN)
/SAM_RESET: U103.9 (IO5), U107.18 (~RESET)
/SENSE_A: R407.1, R409.2, U101.15 (AIN0/GPIO0)
/SENSE_B: R419.1, R421.2, U101.16 (AIN1/GPIO1)
/SENSE_C: R408.1, R410.2, U101.3 (AIN4/GPIO4)
/SENSE_D: R420.1, R422.2, U101.4 (AIN5/GPIO5)
/SPI_MISO: J106.3, U103.7 (IO3), U106.12 (MISO), U301.5 (SDO), U302.1 (SDO/TA0), U303.6 (SDO)
/SPI_MOSI: J106.2, U103.6 (IO2), U106.13 (MOSI), U301.16 (SDI), U302.14 (SDA), U303.7 (SDI/SDA)
/SPI_SCK: J106.1, U103.5 (IO1), U106.15 (SCK), U301.1 (SCK), U302.13 (SCL), U303.8 (SCLK)
/SYS_POWER: C202.1, D202.1 (K), J201.1, R104.1, R206.2, U203.1 (OUT), U203.8 (OUT), U204.4 (EN), U204.6 (IN)
/USB_D+: U102.1 (D+_in), U103.24 (USB_D+)
/USB_D-: U102.2 (D-_in), U103.23 (USB_D-)
/USB_POWER: J101.A4 (VBUS), J101.A9 (VBUS), J101.B4 (VBUS), J101.B9 (VBUS), R201.1, U201.4 (IN), U201.5 (IN), U201.6 (IN), U203.7 (IN1)
/VBAT: J103.6, R203.1, U202.4 (IN), U202.5 (IN), U202.6 (IN), U203.2 (IN2)
/VBAT_PYRO: D101.2 (A), J102.1, R403.1, U401.5 (IN)
/VBAT_SENSE: R104.2, R105.1, U101.6 (AIN7/GPIO7)
/VCAP: C203.1, D202.2 (A), R108.1, R206.1
/VCAP_SENSE: R108.2, R109.1, U101.5 (AIN6/GPIO6)
/V_PYRO: C402.1, J102.3, J102.5, J103.2, J103.4, R413.1, U401.6 (OUT)
GND: BZ101.2 (-), C101.2, C102.2, C103.2, C104.2, C105.2, C106.1, C107.2, C108.2, C109.2, C110.2, C111.2, C112.2, C113.1, C114.1, C202.2, C203.2, C204.2, C301.2, C302.2, C303.2, C304.2, C305.2, C306.2, C401.2, C402.2, C403.1, D102.1 (A1), D103.1 (A1), D104.1 (K), D105.1 (K), D106.1 (K), D107.1 (K), D201.1 (K), D203.1 (K), J101.A1 (GND), J101.A12 (GND), J101.B1 (GND), J101.B12 (GND), J101.S1 (SHIELD), J102.2, J103.5, J104.3, J105.2 (Ext), J108.3, J202.2, L101.2, Q401.1 (S1), Q401.3 (S2), Q402.1 (S1), Q402.3 (S2), R103.2, R105.2, R106.2, R107.2, R109.2, R401.2, R402.2, R404.2, R409.1, R410.1, R411.2, R414.2, R415.2, R416.2, R421.1, R422.1, U101.9 (GND), U101.17 (EPAD), U102.3 (GND), U103.1 (GND), U103.2 (GND), U103.42 (GND), U103.43 (GND), U103.46 (GND), U103.47 (GND), U103.48 (GND), U103.49 (GND), U103.50 (GND), U103.51 (GND), U103.52 (GND), U103.53 (GND), U103.54 (GND), U103.55 (GND), U103.56 (GND), U103.57 (GND), U103.58 (GND), U103.59 (GND), U103.60 (GND), U103.61 (GND), U103.62 (GND), U103.63 (GND), U103.64 (GND), U103.65 (GND), U104.4 (GND), U105.4 (GND), U105.9 (EP), U106.2 (GND), U106.7 (GND), U106.16 (GND), U107.1 (GND), U107.4 (GND), U107.5 (GND), U107.6 (GND), U107.10 (GND), U107.11 (GND), U107.15 (GND), U107.16 (GND), U107.20 (GND), U201.1 (GND), U201.2 (GND), U201.3 (GND), U201.7 (GND), U202.1 (GND), U202.2 (GND), U202.3 (GND), U202.7 (GND), U204.3 (GND), U204.7 (EP), U301.9 (GND), U301.11 (GND), U302.2 (SDx), U302.3 (SCx), U302.6 (GND), U302.7 (GND), U303.2 (PS), U303.3 (GND), U401.8 (GND), U402.6 (GND), U402.15 (A0), U402.16 (A1)
unnamed: D101.1 (K), R102.1
unnamed: D104.2 (A), R121.2
unnamed: D105.2 (A), R122.2
unnamed: D106.2 (A), R123.2
unnamed: D107.2 (A), R124.2
unnamed: D203.2 (A), R207.2
unnamed: J101.A5 (CC1), R106.1
unnamed: J101.B5 (CC2), R107.1
unnamed: J105.1 (In), L101.1, U106.6 (ANT)
unnamed: Q401.2 (G1), R417.2
unnamed: Q401.4 (G2), R405.2
unnamed: Q402.2 (G1), R406.2
unnamed: Q402.4 (G2), R418.2
unnamed: R101.1, U101.11 (ADDR)
unnamed: C101.1, R101.2, U101.8 (DECAP)
unnamed: U106.9 (TXEN), U106.19 (DIO2)
unnamed: R205.2, U203.10 (ILM)
unnamed: R201.2, R202.1, U203.5 (OV1)
unnamed: R203.2, R204.1, U203.4 (OV2)
unnamed: C201.2, U203.11 (SS)
unnamed: C303.1, U301.10 (CAP)
unnamed: R411.1, U401.9 (ILM)
unnamed: C401.1, U401.10 (ITIMER)

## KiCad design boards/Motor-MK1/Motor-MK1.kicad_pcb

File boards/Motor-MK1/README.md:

# MotorBoard

Starting off the year as just a concept, the Motor Board has taken shape as an impressive new piece of the MIDAS ecosystem. Unofficially known as “Spinny Antenna Motor” (SAM) Board, the project serves as a method of control for the team’s SAM Turret antenna tracker, which aims to automatically track the rocket’s position during flight and maintain optimal antenna orientation to get the best possible range for MIDAS telemetry. In addition to cementing MIDAS’s role as an important part of our team’s ground operations, the Motor Board has served as a testbed for WiFi as a new way of board-to-board communication.

Read more about MotorBoard, MIDAS and the surrounding avionics systems in the [MIDAS MK2 Report](https://uofi.box.com/s/k0ad6ryhxbzwpdwt33lxyxuxpivv3qhj).

# Schematics

Printable PDF schematics and layouts for MotorBoard can be found in the PDFs and images folders.

# Photos

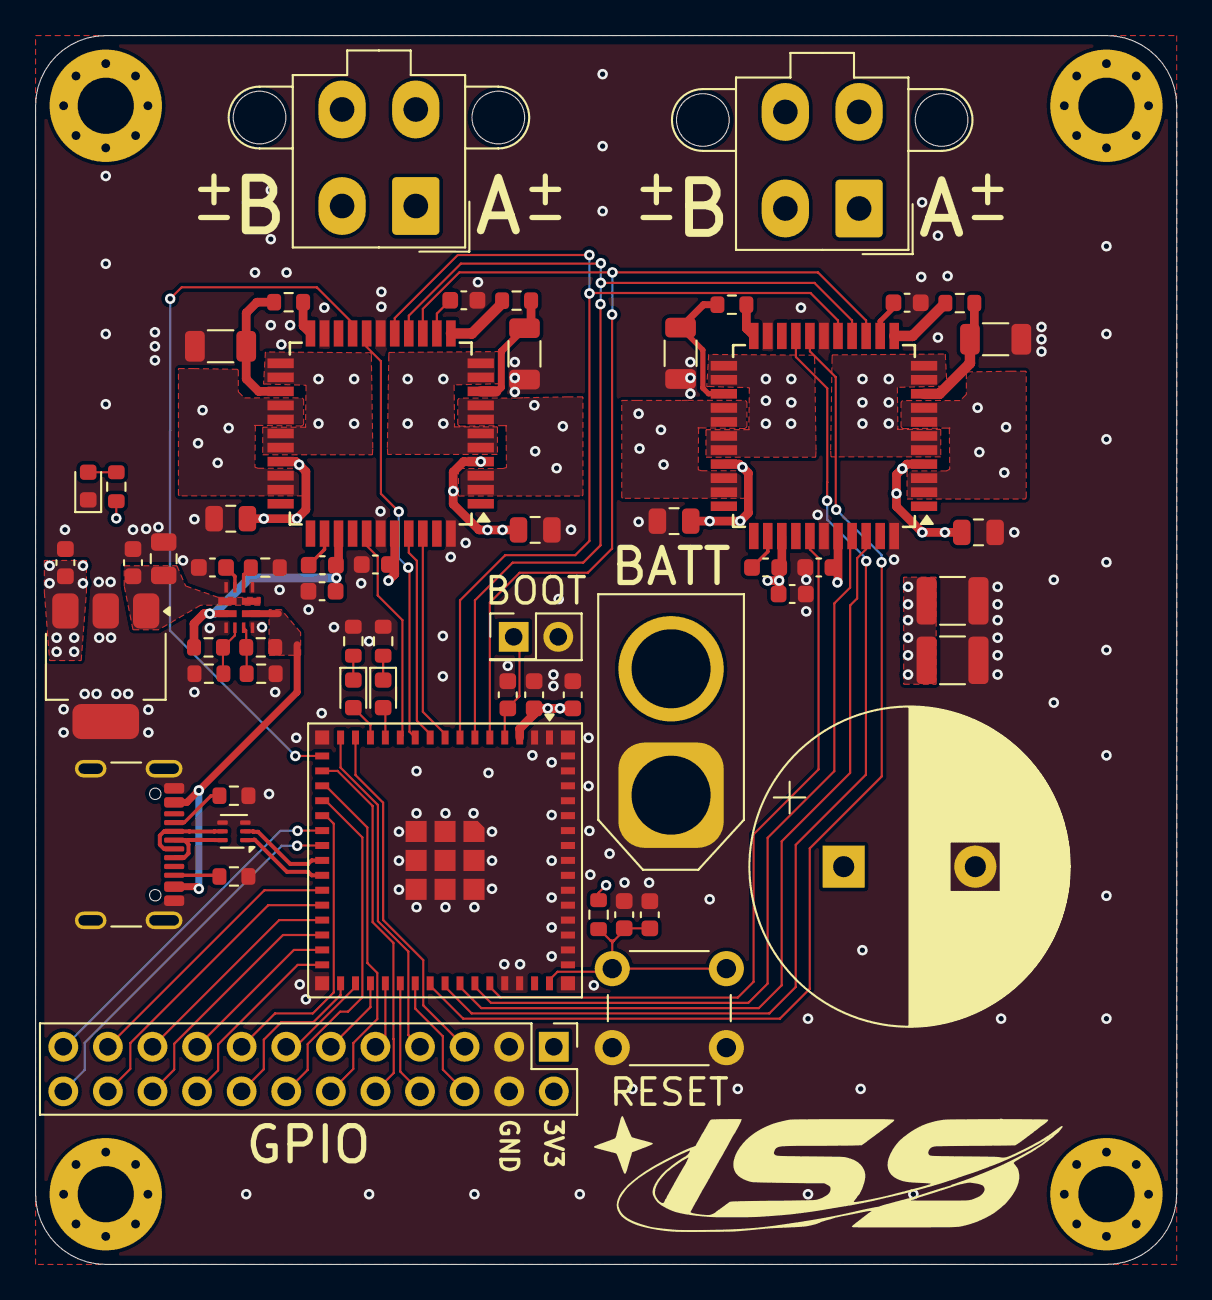
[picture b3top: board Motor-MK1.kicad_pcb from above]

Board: 4 copper layers, 65.0 x 70.0 mm, 63 parts (0 on the bottom side), 75 nets.

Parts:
C1, C6: 470nF; C_0603_1608Metric
C2: 1200uF; CP_Radial_D18.0mm_P7.50mm
C3, C4: 100uF; C_1210_3225Metric
C5, C11, C13, C14, C16: 10uF; C_0805_2012Metric
C7, C9, C10, C12, C18, C102, C103, C104: 100nF; C_0603_1608Metric
C8, C15: 220nF; C_0603_1608Metric
C17, C101: 22uF; C_0603_1608Metric
C105, C206: 1uF; C_0603_1608Metric
D1, D2: LED; LED_0603_1608Metric
D201: RED LED; LED_0603_1608Metric
H1, H2, H3, H4: MountingHole; MountingHole_3.2mm_M3_Pad_Via
J1, J2: Conn_01x04; Molex_Mini-Fit_Jr_5566-04A2_2x02_P4.20mm_Vertical
J3: Conn_02x12_Counter_Clockwise; PinHeader_2x12_P2.54mm_Vertical
J4: Conn_01x02; AMASS_XT60-M_1x02_P7.20mm_Vertical
J101: USB_C_Receptacle_USB2.0_16P; USB_C_Receptacle_GCT_USB4105-xx-A_16P_TopMnt_Horizontal
R1, R3, R5, R6: 10; R_0603_1608Metric
R2, R4, R7, R8: 0.075; R_1206_3216Metric
R9, R10: 470; R_0603_1608Metric
R11: 23.7k; R_0603_1608Metric
R12: 5k; R_0603_1608Metric
R13: 30k; R_0603_1608Metric
R14: 1k; R_0603_1608Metric
R101: 100k; R_0603_1608Metric
R102, R103: 5.1k; R_0603_1608Metric
R201: 470 ohms; R_0603_1608Metric
R214: 20k; R_0603_1608Metric
SW101: SW_Push; PinHeader_2x01_P2.54mm_Vertical
SW102: SW_Push; SW_PUSH_6mm
U1: ESP32-S3-MINI-1U; ESP32-S2-MINI-1U
U2, U3: TMC2660C; TQFP-44_10x10mm_P0.8mm
U4: TLE42744; SOT-223
U102: ECMF02-2AMX6; ST_UQFN-6L_1.5x1.7mm_P0.5mm
U203: TPS2121; VQFN-HR-RUX0012A

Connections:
+3V3: C7.2, C9.2, C17.1, C101.2, C102.2, J3.1, J3.2, R101.1, R201.1, U1.3 (3V3), U2.40 (VCC_IO), U3.40 (VCC_IO), U4.3 (Q)
/D+: J101.A6 (D+), J101.B6 (D+), U102.6 (D+_out)
/D-: J101.A7 (D-), J101.B7 (D-), U102.5 (D-_out)
/DIR_0: U1.9 (IO5), U2.41 (DIR)
/DIR_1: U1.40 (RXD0), U3.41 (DIR)
/GPIO_10: J3.5, U1.14 (IO10)
/GPIO_11: J3.7, U1.15 (IO11)
/GPIO_13: J3.10, U1.17 (IO13)
/GPIO_14: J3.12, U1.18 (IO14)
/GPIO_15: J3.14, U1.19 (IO15)
/GPIO_16: J3.15, U1.20 (IO16)
/GPIO_17: J3.23, U1.21 (IO17)
/GPIO_18: J3.24, U1.22 (IO18)
/GPIO_21: J3.21, U1.25 (IO21)
/GPIO_26: J3.22, U1.26 (IO26)
/GPIO_33: J3.20, U1.28 (IO33)
/GPIO_34: J3.17, U1.29 (IO34)
/GPIO_35: J3.16, U1.31 (IO35)
/GPIO_36: J3.13, U1.32 (IO36)
/GPIO_37: J3.11, U1.33 (IO37)
/GPIO_38: J3.9, U1.34 (IO38)
/GPIO_39: J3.8, U1.35 (IO39)
/GPIO_40: J3.6, U1.36 (IO40)
/GPIO_47: J3.19, U1.27 (IO47)
/GPIO_48: J3.18, U1.30 (IO48)
/Power/SYS_Power: C16.1, C18.1, U4.1 (I), U203.1 (OUT), U203.8 (OUT)
/SCK: U1.7 (IO3), U2.16 (SCK), U3.16 (SCK)
/SDI: U1.6 (IO2), U2.15 (SDI), U3.15 (SDI)
/SDO: U1.5 (IO1), U2.14 (SDO), U3.14 (SDO)
/SG_TST_0: U1.11 (IO7), U2.38 (SG_TST)
/SG_TST_1: U1.41 (IO45), U3.38 (SG_TST)
/STEP_0: U1.8 (IO4), U2.42 (STEP)
/STEP_1: U1.39 (TXD0), U3.42 (STEP)
/USB_POWER: J101.A4 (VBUS), J101.A9 (VBUS), J101.B4 (VBUS), J101.B9 (VBUS), R11.1, U203.7 (IN1)
/VBAT: C2.1, C3.1, C4.1, C5.1, C8.1, C10.1, C11.1, C12.1, C13.1, C14.1, C15.1, J4.2, R13.1, U2.4 (VSA), U2.30 (VSB), U2.36 (VS), U3.4 (VSA), U3.30 (VSB), U3.36 (VS), U203.2 (IN2)
/~CS_0: U1.10 (IO6), U2.18 (~CS)
/~CS_1: U1.37 (IO41), U3.18 (~CS)
/~EN_0: U1.16 (IO12), U2.19 (~EN)
/~EN_1: U1.38 (IO42), U3.19 (~EN)
BOOT_SW: C103.1, SW101.1, U1.4 (IO0)
GND: C1.2, C2.2, C3.2, C4.2, C5.2, C6.2, C7.1, C9.1, C10.2, C11.2, C12.2, C13.2, C14.2, C16.2, C17.2, C18.2, C101.1, C102.1, C103.2, C104.2, C105.2, C206.2, D201.1 (K), J3.3, J3.4, J4.1, J101.A1 (GND), J101.A12 (GND), J101.B1 (GND), J101.B12 (GND), J101.S1 (SHIELD), R2.2, R4.2, R7.2, R8.2, R9.2, R10.2, R12.2, R14.2, R102.2, R103.2, R214.2, SW101.2, SW102.2, U1.1 (GND), U1.2 (GND), U1.42 (GND), U1.43 (GND), U1.46 (GND), U1.47 (GND), U1.48 (GND), U1.49 (GND), U1.50 (GND), U1.51 (GND), U1.52 (GND), U1.53 (GND), U1.54 (GND), U1.55 (GND), U1.56 (GND), U1.57 (GND), U1.58 (GND), U1.59 (GND), U1.60 (GND), U1.61 (GND), U1.62 (GND), U1.63 (GND), U1.64 (GND), U1.65 (GND), U2.17 (GND), U2.21 (CLK), U2.39 (GND), U2.44 (GND), U3.17 (GND), U3.21 (CLK), U3.39 (GND), U3.44 (GND), U4.2 (GND), U4.4 (GND), U102.3 (GND), U102.4 (NC), U203.3 (CP2), U203.6 (PR1), U203.9 (ST), U203.12 (GND)
unnamed: D1.2 (A), U1.13 (IO9)
unnamed: D1.1 (K), R9.1
unnamed: D2.2 (A), U1.12 (IO8)
unnamed: D2.1 (K), R10.1
unnamed: D201.2 (A), R201.2
unnamed: J1.1, U2.5 (OA2), U2.6 (OA2), U2.10 (OA2), U2.11 (OA2)
unnamed: J1.2, U2.23 (OB2), U2.24 (OB2), U2.28 (OB2), U2.29 (OB2)
unnamed: J1.3, U2.2 (OA1), U2.3 (OA1), U2.7 (OA1), U2.8 (OA1)
unnamed: J1.4, U2.26 (OB1), U2.27 (OB1), U2.31 (OB1), U2.32 (OB1)
unnamed: J2.1, U3.5 (OA2), U3.6 (OA2), U3.10 (OA2), U3.11 (OA2)
unnamed: J2.2, U3.23 (OB2), U3.24 (OB2), U3.28 (OB2), U3.29 (OB2)
unnamed: J2.3, U3.2 (OA1), U3.3 (OA1), U3.7 (OA1), U3.8 (OA1)
unnamed: J2.4, U3.26 (OB1), U3.27 (OB1), U3.31 (OB1), U3.32 (OB1)
unnamed: J101.A5 (CC1), R102.1
unnamed: J101.B5 (CC2), R103.1
unnamed: C1.1, U2.13 (5VOUT)
unnamed: R1.2, R2.1, U2.9 (BRA)
unnamed: R3.2, R4.1, U2.25 (BRB)
unnamed: R1.1, U2.12 (SRA)
unnamed: R3.1, U2.22 (SRB)
unnamed: C8.2, U2.35 (VHS)
unnamed: C6.1, U3.13 (5VOUT)
unnamed: R5.2, R7.1, U3.9 (BRA)
unnamed: R6.2, R8.1, U3.25 (BRB)
unnamed: R5.1, U3.12 (SRA)
unnamed: R6.1, U3.22 (SRB)
unnamed: C15.2, U3.35 (VHS)
unnamed: R214.1, U203.10 (ILM)
unnamed: R11.2, R12.1, U203.5 (OV1)
unnamed: R13.2, R14.1, U203.4 (OV2)
unnamed: C206.1, U203.11 (SS)
RESET_SW: C104.1, C105.1, R101.2, SW102.1, U1.45 (EN)
USB+: U1.24 (IO20), U102.1 (D+_in)
USB-: U1.23 (IO19), U102.2 (D-_in)
